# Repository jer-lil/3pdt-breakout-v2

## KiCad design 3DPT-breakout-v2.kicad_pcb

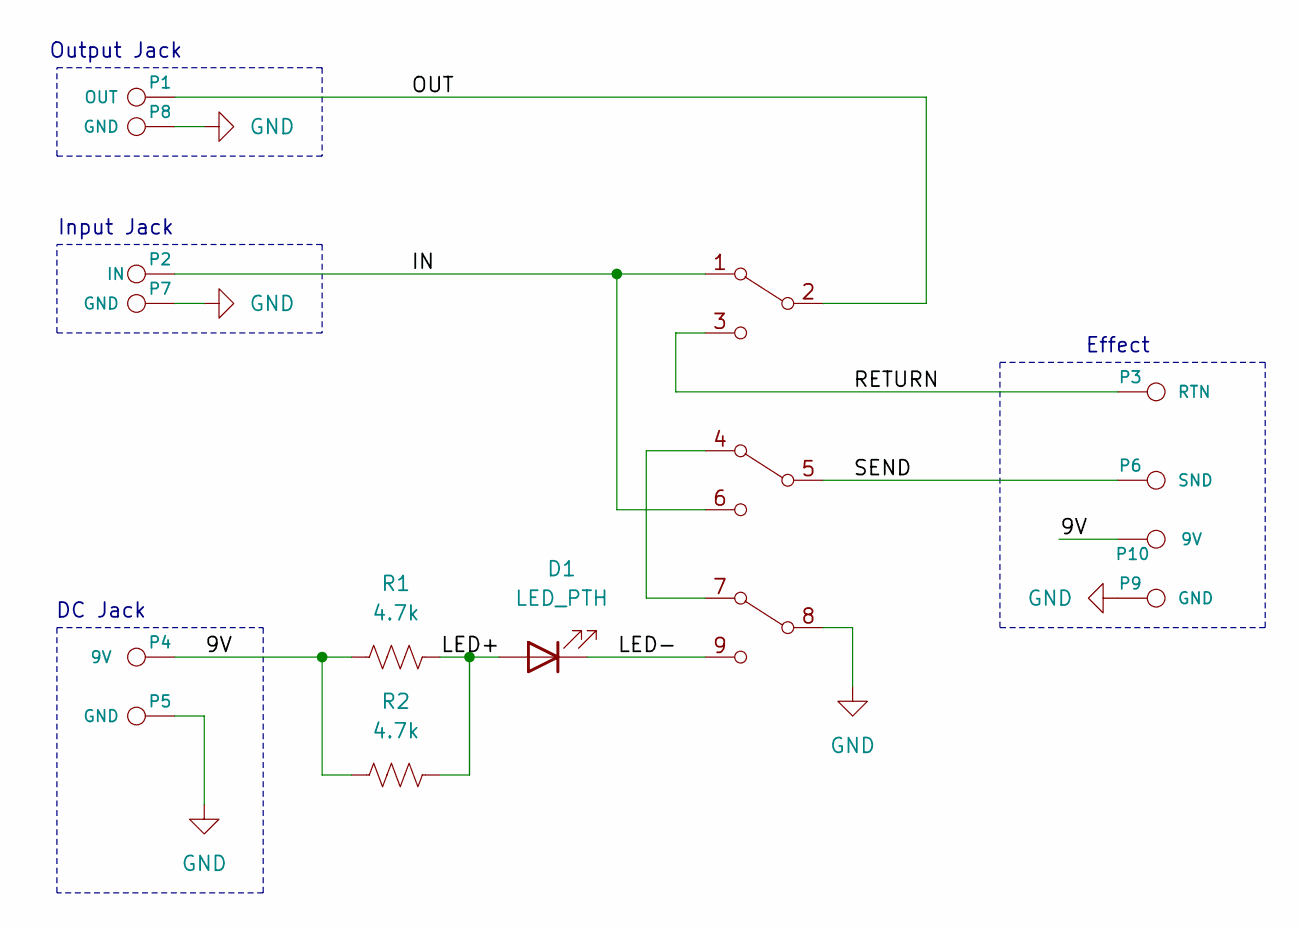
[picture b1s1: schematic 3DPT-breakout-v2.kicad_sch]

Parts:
D1: LED_PTH; LED_D5.0mm
P1: OUT; WirePad_22AWG
P2: IN; WirePad_22AWG
P3: RTN; WirePad_22AWG
P4, P10: 9V; WirePad_22AWG
P5, P7, P8, P9: GND; WirePad_22AWG
P6: SND; WirePad_22AWG
R1: 4.7k; R_Axial_DIN0207_L6.3mm_D2.5mm_P7.5mm_Horizontal
R2: 4.7k; R_0805_2012Metric_Pad1.20x1.40mm_HandSolder
SW1: SW_3PDT; SW_STOMP_3PDT

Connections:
/9V: P4.1, P10.1, R1.1, R2.1
/IN: P2.1, SW1.1 (A), SW1.6 (C)
/LED+: D1.2 (A), R1.2, R2.2
/LED-: D1.1 (K), SW1.9 (C)
/OUT: P1.1, SW1.2 (B)
/RETURN: P3.1, SW1.3 (C)
/SEND: P6.1, SW1.5 (B)
GND: P5.1, P7.1, P8.1, P9.1, SW1.8 (B)
unnamed: SW1.4 (A), SW1.7 (A)

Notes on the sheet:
DC Jack
Input Jack
Output Jack
Effect

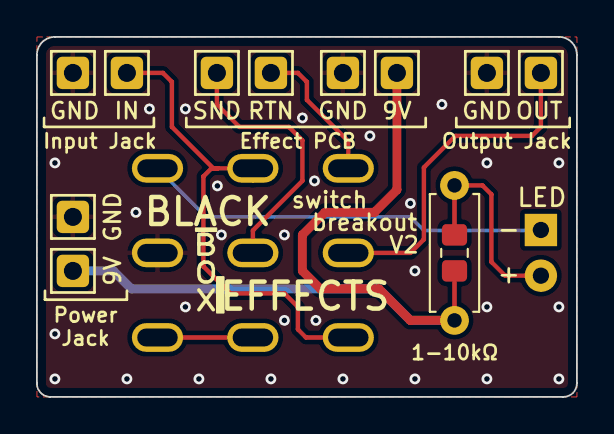
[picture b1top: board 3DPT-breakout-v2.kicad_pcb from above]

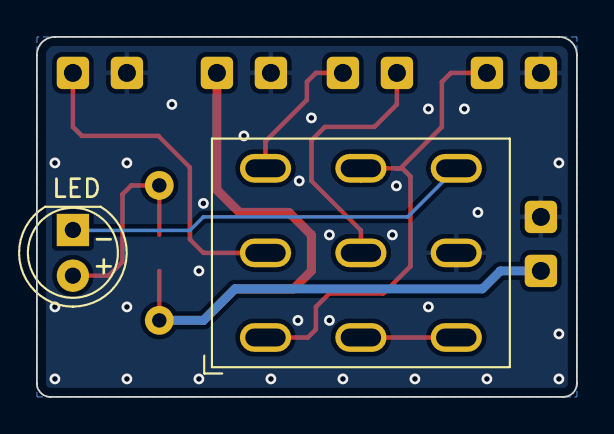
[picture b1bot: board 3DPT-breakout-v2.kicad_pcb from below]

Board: 2 copper layers, 30.0 x 20.0 mm, 14 parts (2 on the bottom side), 9 nets.

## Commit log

2024-05-20 one and done
    oops I did the whole thing
    generated gerbers, but waiting to order
2026-01-04 Gerbers
